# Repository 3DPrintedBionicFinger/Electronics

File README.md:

# Electronics
Electronics and prototype test code.

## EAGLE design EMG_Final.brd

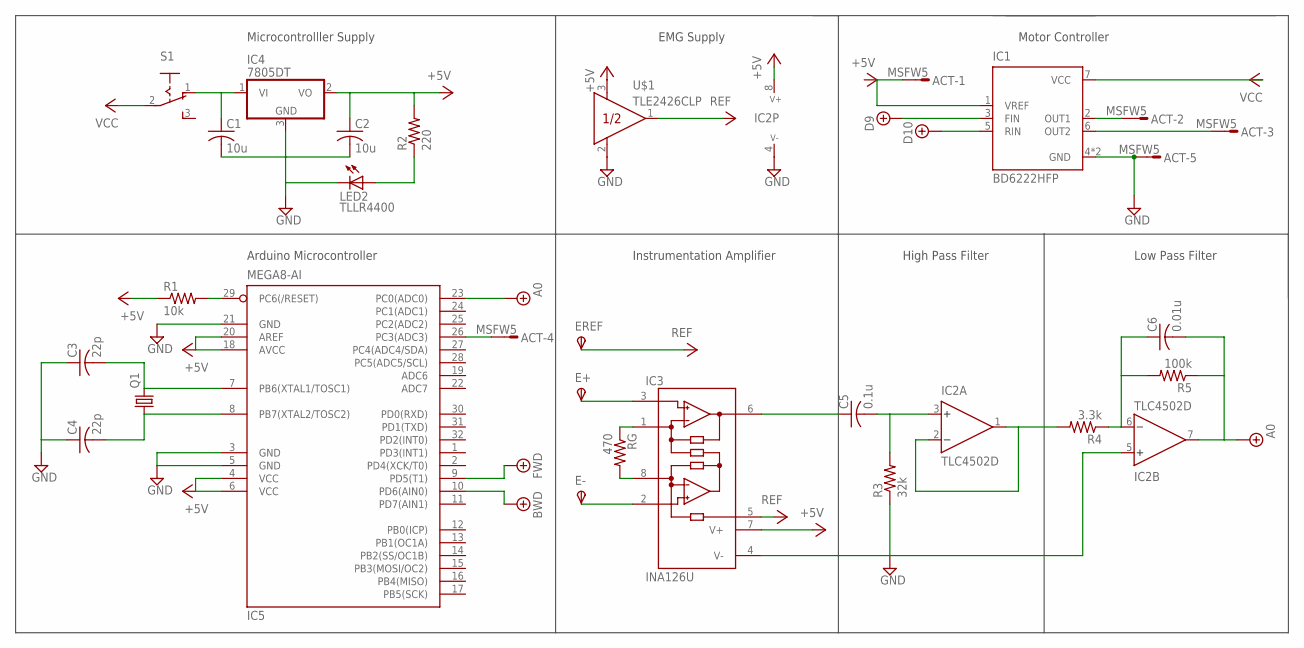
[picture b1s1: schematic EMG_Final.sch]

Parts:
ACT: MSFW5
C1, C2: 10u; C0603
C3, C4: 22p; C0603
C5: 0.1u; C0603
C6: 0.01u; C0603
E+: TPSPAD1-13; P1-13
E-: TPSPAD1-13; P1-13
EREF: TPSPAD1-13; P1-13
IC1: BD6222HFP; HRP7
IC2: TLC4502D; D_R-PDSO-G08
IC3: INA126U; SO08
IC4: 7805DT; TO252
IC5: MEGA8-AI; TQFP32-08
LED2: TLLR4400; LED3MM
Q1: CRYSTALMM20SS; MM20SS
R1: 10k; R0603
R2: 220; R0603
R3: 32k; R0603
R4: 3.3k; R0603
R5: 100k; R0603
RG: 470; R0603
S1: 255SB
U$1: TLE2426CLP; TO226AA

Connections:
+3V3: EREF.TP, IC3.5 (REF), U$1.1 (OUT)
+5V: C2.1, IC2.8 (V+), IC3.7 (V+), IC4.2 (VO), IC5.4 (VCC), IC5.6 (VCC), IC5.18 (AVCC), IC5.20 (AREF), R1.1, R2.2, U$1.3 (IN)
+5V/1: C6.2, IC2.7 (OUT), IC5.23 (PC0(ADC0)), R5.1
+10V: IC1.3 (FIN), IC5.9 (PD5(T1))
+12V: IC1.5 (RIN), IC5.10 (PD6(AIN0))
GND: ACT.5, C1.2, C2.2, C3.1, C4.1, IC1.4 (GND), IC1.P (GND), IC2.4 (V-), IC2.5 (+), IC3.4 (V-), IC4.3 (GND), IC5.3 (GND), IC5.5 (GND), IC5.21 (GND), LED2.K (C), R3.1, U$1.2 (COM)
unnamed: C1.1, IC4.1 (VI), S1.1 (O)
unnamed: C3.2, IC5.7 (PB6(XTAL1/TOSC1)), Q1.4 (2)
unnamed: C4.2, IC5.8 (PB7(XTAL2/TOSC2)), Q1.1
unnamed: IC5.29 (PC6(/RESET)), R1.2
unnamed: LED2.A, R2.1
unnamed: C5.1, IC3.6 (OUT)
unnamed: C5.2, IC2.3 (+), R3.2
unnamed: IC2.1 (OUT), IC2.2 (-), R4.2
unnamed: C6.1, IC2.6 (-), R4.1, R5.2
unnamed: ACT.1, IC1.1 (VREF)
unnamed: IC3.8 (RG), RG.2
unnamed: IC3.1 (RG), RG.1
unnamed: ACT.2, IC1.2 (OUT1)
unnamed: E+.TP, IC3.3 (+IN)
unnamed: E-.TP, IC3.2 (-IN)
unnamed: ACT.4, IC5.26 (PC3(ADC3))
unnamed: ACT.3, IC1.6 (OUT2)
VCC: IC1.7 (VCC), S1.2

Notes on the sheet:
Instrumentation Amplifier
High Pass Filter
Low Pass Filter
Arduino Microcontroller
Microcontrolller Supply
EMG Supply
Motor Controller

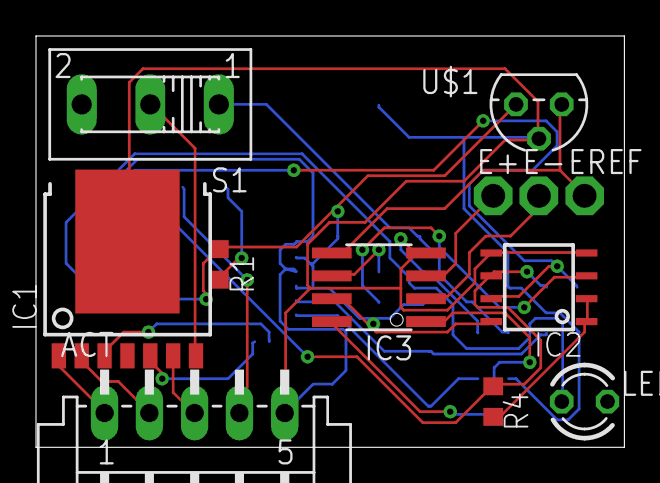
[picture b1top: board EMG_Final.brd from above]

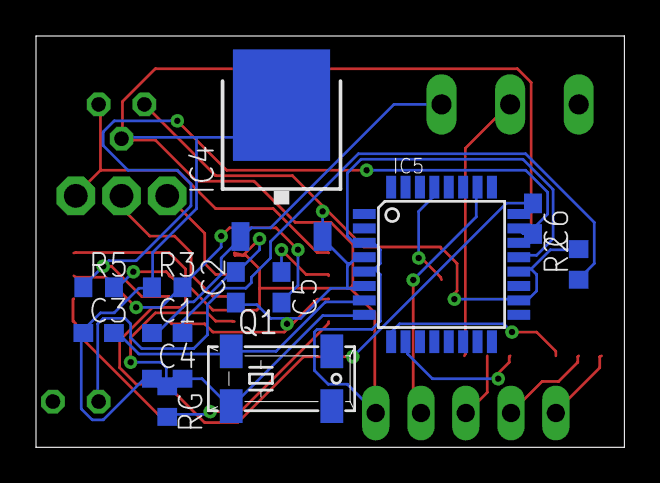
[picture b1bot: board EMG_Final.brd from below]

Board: 2 copper layers, 32.7 x 22.9 mm, 25 parts (13 on the bottom side), 24 nets.

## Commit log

2018-04-11 Create LICENSE
